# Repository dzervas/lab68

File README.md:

# Dissatisfaction65
<center>
  
</center>
This is the hardware repository for my 65% QMK Bluetooth keyboard with an OLED and encoder.

**I'm working on a new version of this to vastly improve the design and functionality. You can follow the development on [this discord](https://discord.gg/mYy7CFR)**

# Software (QMK)
You can currently find the firmware for this board at [my qmk-firmware fork](https://github.com/Nicell/qmk_firmware/tree/dissatisfaction-65). It requires [this pull-request](https://github.com/qmk/qmk_firmware/pull/7769) before it can be fully upstreamed.

# What you'll need (or at least what I used)
You can get most of these items at different places, but I left the more convenient places here. Often you can get cheaper electronics at LCSC and AliExpress rather than Mouser and Amazon.
 - Adafruit Feather 32u4 Bluefruit LE [BUY](https://www.amazon.com/Adafruit-Feather-32u4-Bluefruit-ADA2829/dp/B01GJR9MNI)
 - 2500mAH battery or equivalent (probably don't go thicker) [BUY](https://www.amazon.com/Adafruit-328-Battery-Lithium-Polymer/dp/B01NAX9XYG)
 - EC12 Encoder Knob [BUY](https://www.amazon.com/Cylewet-Encoder-Digital-Potentiometer-Arduino/dp/B07DM2YMT4)
 - OLED SSD1306 128x32 [BUY](https://www.amazon.com/MakerFocus-Display-SSD1306-3-3V-5V-Arduino/dp/B079BN2J8V)
 - Long headers for the OLED to reach far down [BUY](https://www.mouser.com/ProductDetail/fci-amphenol/68653-105hlf)
 - 1N4148 DO-35 package 67x [BUY](https://www.mouser.com/ProductDetail/on-semiconductor/1n4148tr)
 - 74HC4515 Decoder [BUY](https://www.mouser.com/ProductDetail/nexperia/74hc4515d653)
 - On-Off switch [BUY](https://www.mouser.com/ProductDetail/alps/sddjf1a100)
 - Encoder Knob [BUY](https://www.amazon.com/dp/B07Z1MQ9T7)
 - M3 ([Bolts](https://www.amazon.com/gp/product/B075CFBHWV)) ([Nuts](https://www.amazon.com/gp/product/B01IWUSDYY)) ([Lock Nuts](https://www.amazon.com/gp/product/B07MD7SPBJ)) ([Rubber Feet](https://www.amazon.com/gp/product/B07CNQC695))
 - Plates: one of each of the plates found in the DXF folder. Middle MUST be 1.5mm. I got mine from SendCutSend in brushed stainless steel using the combined plates file. I highly recommend them. Fast, affordable, and good quality.
 - Middle pieces: 7x of the middle piece found in the DXF folder. I used 1/8in thick pieces. 2x between the top and switch plate, and 5x between the bottom and switch plate. The second and third to last from the bottom pieces need cutouts for both the micro USB and the power switch. I got mine from Sculpteo. I would not recommend them. The wait was long, the order was messed up, and the quality was very mediocre. There was an obvious taper on the cuts.
 - MX style switches 67x. PCB or plate mount
 - Keycaps! KLE can be found [here](http://www.keyboard-layout-editor.com/#/gists/c38820c1ede8c90e253ba465600c6e75).

# Things I'd like to change
There were a few things that I'd like to change. I haven't done them yet, but they would enhance the board.
 - Move the encoder switch to the matrix. Currently has its own direct connection.
 - Recreate the switch plate using ai03's plate designer. Currently has huge lines across stabs and the stab holes are really tight.
 - Re-dimension the OLED. It seems to be barely too far down and to the left. I can re-dimension now that I have calipers.
 - Redo the decoder using a 74HC154. No need to use the latched version that's more expensive and slower.
 - Create a little cut in the middle pieces to use as a prop up for the OLED.
 - Create pre-made middle pieces with cutouts for the micro USB port and the on-off switch rather than cutting them manually.

# Random things I encountered
 - Make sure to test your Adafruit board fully before soldering it in. The board I got had a working MCU and Bluetooth module, but they couldn't communicate properly despite continuity between the SPI pins.
 - My plate ended up flexing a bit when connecting the switches. I suspect the PCB was either a bit too small or the plate was a bit too big. I really don't know why this was the case.

# Thanks to
 - QMK team for helping me with getting the firmware working
 - Nick_68 and WoodKeys for each of their iterations on the Bluetooth + decoder design with the Ronin and Meira, which were invaluable for me while I was designing this board.
 - ai03 for the MX KiCad library I have in this project.

OLED 3D Model: https://grabcad.com/library/oled-0-91-128x32-1
Rotary Encoder 3D Model: https://grabcad.com/library/ec11-rotary-encoder-with-switch-1
MX Switches & stabilizers 3D Models: https://github.com/perigoso/keyswitch-kicad-library

# Images

# Fusion 360 Prepare Board Model

1. Export STEP with KicadStepUp (FreeCAD)
2. Import it in an empty document
3. Create a rigid group between all components
4. Align the group to true origin (using 2 faces)

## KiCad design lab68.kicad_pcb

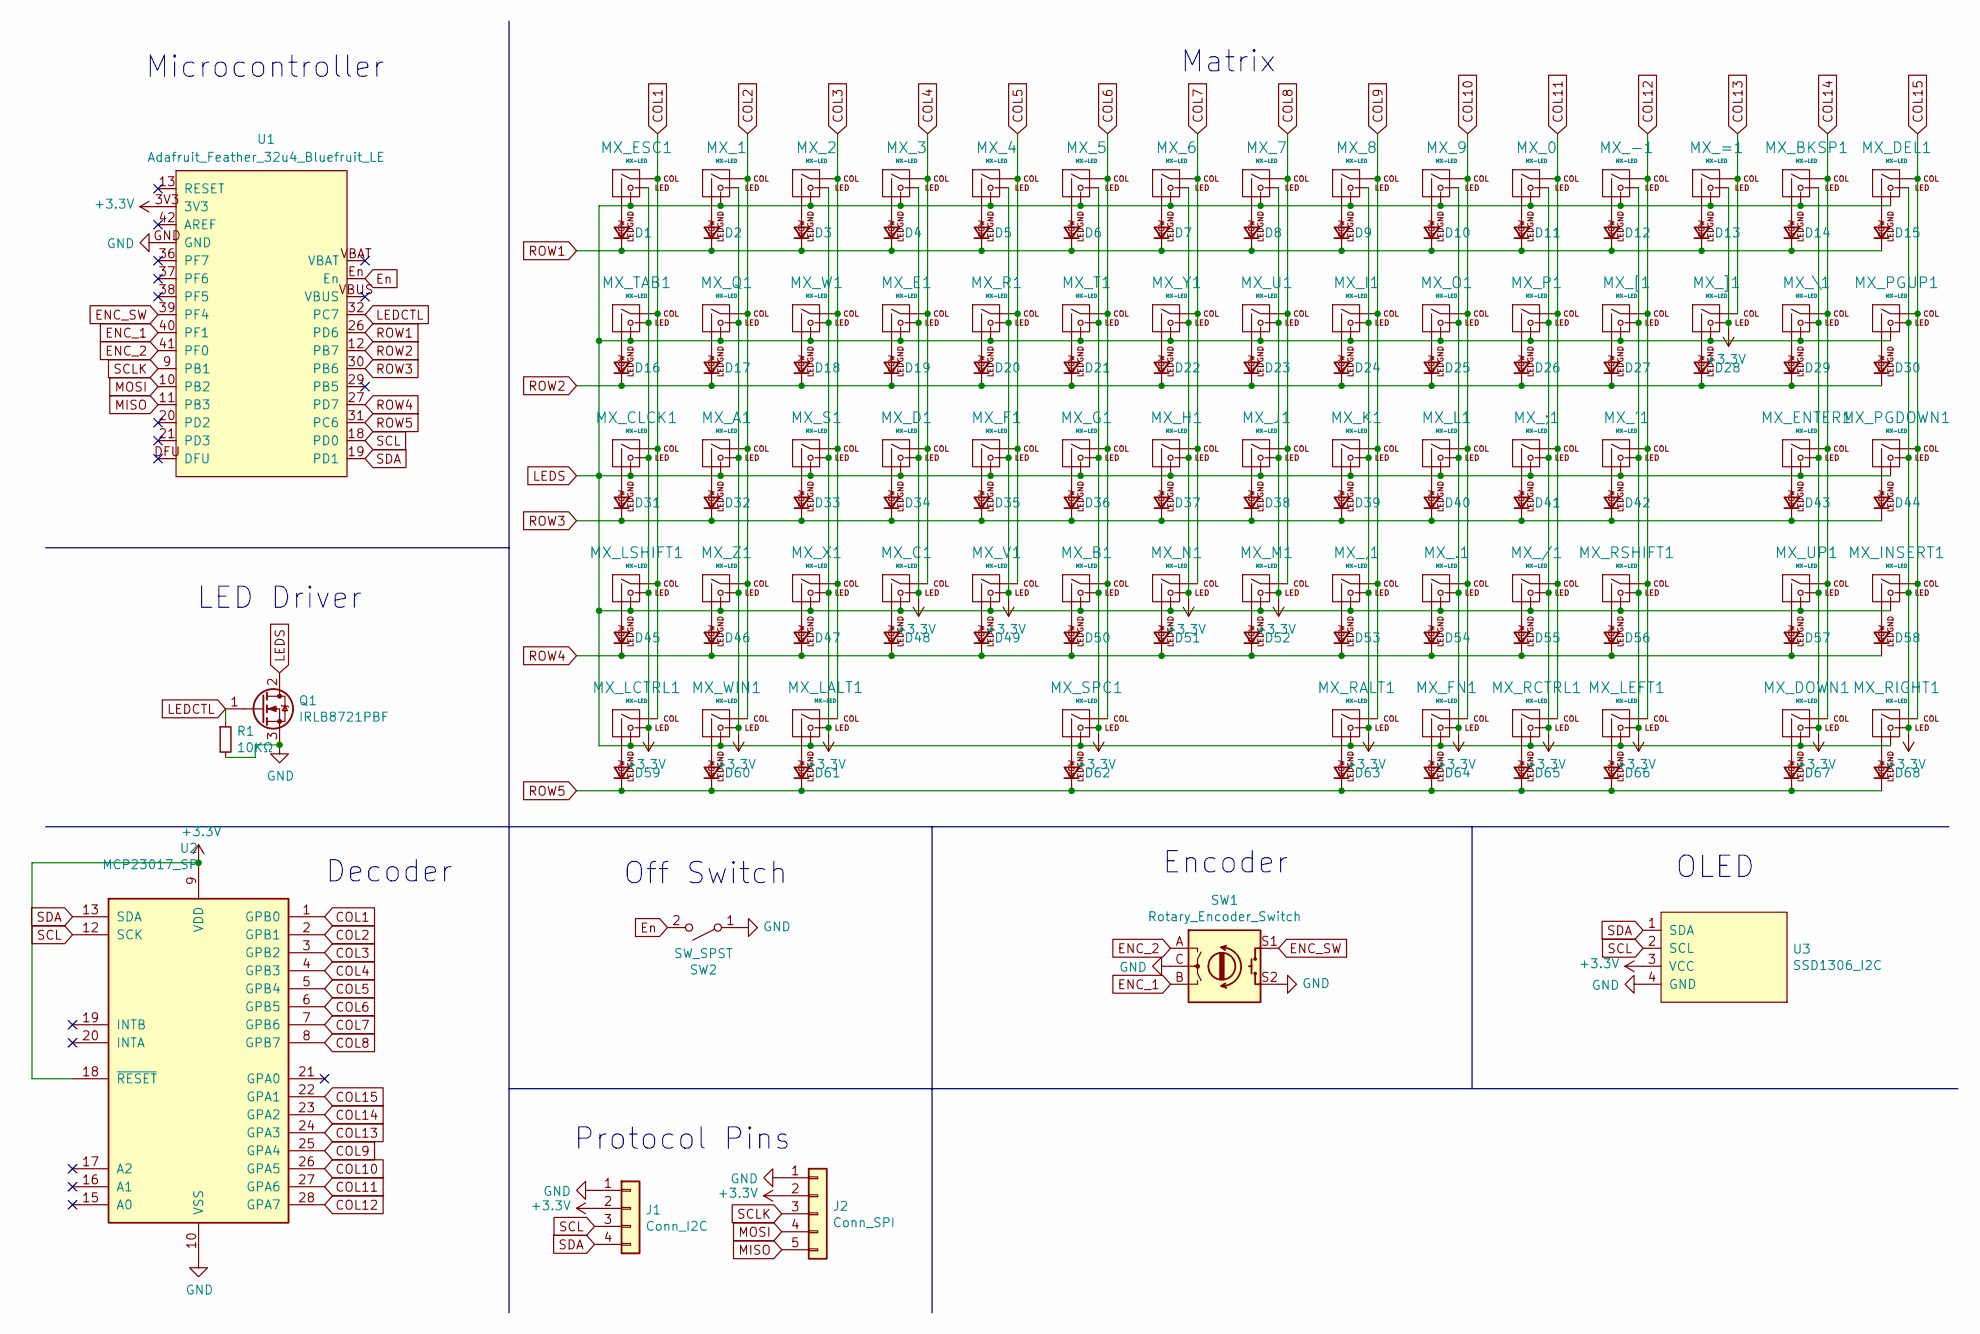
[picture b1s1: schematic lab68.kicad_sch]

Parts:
D1, D2, D3, D4, D5, D6, D7, D8, D9, D10, D11, D12, D13, D14, D15, D16, D17, D18, D19, D20, D21, D22, D23, D24, D25, D26, D27, D28, D29, D30, D31, D32, D33, D34, D35, D36, D37, D38, D39, D40, D41, D42, D43, D44, D45, D46, D47, D48, D49, D50, D51, D52, D53, D54, D55, D56, D57, D58, D59, D60, D61, D62, D63, D64, D65, D66, D67, D68: D_Small; D_DO-35_SOD27_P7.62mm_Horizontal
J1: Conn_I2C; JST_XH_B4B-XH-A_1x04_P2.50mm_Vertical
J2: Conn_SPI; JST_XH_B5B-XH-A_1x05_P2.50mm_Vertical
MX_0, MX_1, MX_2, MX_3, MX_4, MX_5, MX_6, MX_7, MX_8, MX_9, MX_.1: MX-LED; MXOnly-1U
MX_'1: MX-LED; MXOnly-1U
MX_,1: MX-LED; MXOnly-1U
MX_-1: MX-LED; MXOnly-1U
MX_/1: MX-LED; MXOnly-1U
MX_;1: MX-LED; MXOnly-1U
MX_=1: MX-LED; MXOnly-1U
MX_A1: MX-LED; MXOnly-1U
MX_B1: MX-LED; MXOnly-1U
MX_BKSP1: MX-LED; MXOnly-2U
MX_C1: MX-LED; MXOnly-1U
MX_CLCK1: MX-LED; MXOnly-1.75U
MX_D1: MX-LED; MXOnly-1U
MX_DEL1: MX-LED; MXOnly-1U
MX_DOWN1: MX-LED; MXOnly-1U
MX_E1: MX-LED; MXOnly-1U
MX_ENTER1: MX-LED; MXOnly-2.25U
MX_ESC1: MX-LED; MXOnly-1U
MX_F1: MX-LED; MXOnly-1U
MX_FN1: MX-LED; MXOnly-1U
MX_G1: MX-LED; MXOnly-1U
MX_H1: MX-LED; MXOnly-1U
MX_I1: MX-LED; MXOnly-1U
MX_INSERT1: MX-LED; MXOnly-1U
MX_J1: MX-LED; MXOnly-1U
MX_K1: MX-LED; MXOnly-1U
MX_L1: MX-LED; MXOnly-1U
MX_LALT1: MX-LED; MXOnly-1.25U
MX_LCTRL1: MX-LED; MXOnly-1.25U
MX_LEFT1: MX-LED; MXOnly-1U
MX_LSHIFT1: MX-LED; MXOnly-2.25U
MX_M1: MX-LED; MXOnly-1U
MX_N1: MX-LED; MXOnly-1U
MX_O1: MX-LED; MXOnly-1U
MX_P1: MX-LED; MXOnly-1U
MX_PGDOWN1: MX-LED; MXOnly-1U
MX_PGUP1: MX-LED; MXOnly-1U
MX_Q1: MX-LED; MXOnly-1U
MX_R1: MX-LED; MXOnly-1U
MX_RALT1: MX-LED; MXOnly-1U
MX_RCTRL1: MX-LED; MXOnly-1U
MX_RIGHT1: MX-LED; MXOnly-1U
MX_RSHIFT1: MX-LED; MXOnly-1.75U
MX_S1: MX-LED; MXOnly-1U
MX_SPC1: MX-LED; MXOnly-6.25U-ReversedStabilizers
MX_T1: MX-LED; MXOnly-1U
MX_TAB1: MX-LED; MXOnly-1.5U
MX_U1: MX-LED; MXOnly-1U
MX_UP1: MX-LED; MXOnly-1U
MX_V1: MX-LED; MXOnly-1U
MX_W1: MX-LED; MXOnly-1U
MX_WIN1: MX-LED; MXOnly-1.25U
MX_X1: MX-LED; MXOnly-1U
MX_Y1: MX-LED; MXOnly-1U
MX_Z1: MX-LED; MXOnly-1U
MX_[1: MX-LED; MXOnly-1U
MX_\1: MX-LED; MXOnly-1.5U
MX_]1: MX-LED; MXOnly-1U
Q1: IRLB8721PBF; TO-220-3_Horizontal_TabDown
R1: 10KΩ; R_Axial_DIN0207_L6.3mm_D2.5mm_P7.62mm_Horizontal
SW1: Rotary_Encoder_Switch; RotaryEncoder_Alps_EC11E-Switch_Vertical_H20mm
SW2: SW_SPST; SW_CuK_JS202011AQN_DPDT_Angled
U1: Adafruit_Feather_32u4_Bluefruit_LE
U2: MCP23017_SP; DIP-28_W7.62mm_Socket_LongPads
U3: SSD1306_I2C; OLED

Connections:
+3V3: J1.2, J2.2, MX_0.3 (LED), MX_1.3 (LED), MX_2.3 (LED), MX_3.3 (LED), MX_4.3 (LED), MX_5.3 (LED), MX_6.3 (LED), MX_7.3 (LED), MX_8.3 (LED), MX_9.3 (LED), MX_'1.3 (LED), MX_,1.3 (LED), MX_-1.3 (LED), MX_.1.3 (LED), MX_/1.3 (LED), MX_;1.3 (LED), MX_=1.3 (LED), MX_A1.3 (LED), MX_B1.3 (LED), MX_BKSP1.3 (LED), MX_C1.3 (LED), MX_CLCK1.3 (LED), MX_D1.3 (LED), MX_DEL1.3 (LED), MX_DOWN1.3 (LED), MX_E1.3 (LED), MX_ENTER1.3 (LED), MX_ESC1.3 (LED), MX_F1.3 (LED), MX_FN1.3 (LED), MX_G1.3 (LED), MX_H1.3 (LED), MX_I1.3 (LED), MX_INSERT1.3 (LED), MX_J1.3 (LED), MX_K1.3 (LED), MX_L1.3 (LED), MX_LALT1.3 (LED), MX_LCTRL1.3 (LED), MX_LEFT1.3 (LED), MX_LSHIFT1.3 (LED), MX_M1.3 (LED), MX_N1.3 (LED), MX_O1.3 (LED), MX_P1.3 (LED), MX_PGDOWN1.3 (LED), MX_PGUP1.3 (LED), MX_Q1.3 (LED), MX_R1.3 (LED), MX_RALT1.3 (LED), MX_RCTRL1.3 (LED), MX_RIGHT1.3 (LED), MX_RSHIFT1.3 (LED), MX_S1.3 (LED), MX_SPC1.3 (LED), MX_T1.3 (LED), MX_TAB1.3 (LED), MX_U1.3 (LED), MX_UP1.3 (LED), MX_V1.3 (LED), MX_W1.3 (LED), MX_WIN1.3 (LED), MX_X1.3 (LED), MX_Y1.3 (LED), MX_Z1.3 (LED), MX_[1.3 (LED), MX_\1.3 (LED), MX_]1.3 (LED), U1.3V3, U2.9 (VDD), U2.18 (~RESET), U3.3 (VCC)
COL1: MX_CLCK1.1 (COL), MX_ESC1.1 (COL), MX_LCTRL1.1 (COL), MX_LSHIFT1.1 (COL), MX_TAB1.1 (COL), U2.1 (GPB0)
COL2: MX_1.1 (COL), MX_A1.1 (COL), MX_Q1.1 (COL), MX_WIN1.1 (COL), MX_Z1.1 (COL), U2.2 (GPB1)
COL3: MX_2.1 (COL), MX_LALT1.1 (COL), MX_S1.1 (COL), MX_W1.1 (COL), MX_X1.1 (COL), U2.3 (GPB2)
COL4: MX_3.1 (COL), MX_C1.1 (COL), MX_D1.1 (COL), MX_E1.1 (COL), U2.4 (GPB3)
COL5: MX_4.1 (COL), MX_F1.1 (COL), MX_R1.1 (COL), MX_V1.1 (COL), U2.5 (GPB4)
COL6: MX_5.1 (COL), MX_B1.1 (COL), MX_G1.1 (COL), MX_SPC1.1 (COL), MX_T1.1 (COL), U2.6 (GPB5)
COL7: MX_6.1 (COL), MX_H1.1 (COL), MX_N1.1 (COL), MX_Y1.1 (COL), U2.7 (GPB6)
COL8: MX_7.1 (COL), MX_J1.1 (COL), MX_M1.1 (COL), MX_U1.1 (COL), U2.8 (GPB7)
COL9: MX_8.1 (COL), MX_,1.1 (COL), MX_I1.1 (COL), MX_K1.1 (COL), MX_RALT1.1 (COL), U2.25 (GPA4)
COL10: MX_9.1 (COL), MX_.1.1 (COL), MX_FN1.1 (COL), MX_L1.1 (COL), MX_O1.1 (COL), U2.26 (GPA5)
COL11: MX_0.1 (COL), MX_/1.1 (COL), MX_;1.1 (COL), MX_P1.1 (COL), MX_RCTRL1.1 (COL), U2.27 (GPA6)
COL12: MX_'1.1 (COL), MX_-1.1 (COL), MX_LEFT1.1 (COL), MX_RSHIFT1.1 (COL), MX_[1.1 (COL), U2.28 (GPA7)
COL13: MX_=1.1 (COL), MX_]1.1 (COL), U2.24 (GPA3)
COL14: MX_BKSP1.1 (COL), MX_DOWN1.1 (COL), MX_ENTER1.1 (COL), MX_UP1.1 (COL), MX_\1.1 (COL), U2.23 (GPA2)
COL15: MX_DEL1.1 (COL), MX_INSERT1.1 (COL), MX_PGDOWN1.1 (COL), MX_PGUP1.1 (COL), MX_RIGHT1.1 (COL), U2.22 (GPA1)
ENC_1: SW1.B, U1.40 (PF1)
ENC_2: SW1.A, U1.41 (PF0)
ENC_SW: SW1.S1, U1.39 (PF4)
En: SW2.2 (B), U1.En
GND: J1.1, J2.1, Q1.3 (S), R1.2, SW1.C, SW1.S2, SW2.1 (A), U1.GND, U2.10 (VSS), U3.4 (GND)
LEDCTL: Q1.1 (G), R1.1, U1.32 (PC7)
LEDS: MX_0.4 (LEDGND), MX_1.4 (LEDGND), MX_2.4 (LEDGND), MX_3.4 (LEDGND), MX_4.4 (LEDGND), MX_5.4 (LEDGND), MX_6.4 (LEDGND), MX_7.4 (LEDGND), MX_8.4 (LEDGND), MX_9.4 (LEDGND), MX_'1.4 (LEDGND), MX_,1.4 (LEDGND), MX_-1.4 (LEDGND), MX_.1.4 (LEDGND), MX_/1.4 (LEDGND), MX_;1.4 (LEDGND), MX_=1.4 (LEDGND), MX_A1.4 (LEDGND), MX_B1.4 (LEDGND), MX_BKSP1.4 (LEDGND), MX_C1.4 (LEDGND), MX_CLCK1.4 (LEDGND), MX_D1.4 (LEDGND), MX_DEL1.4 (LEDGND), MX_DOWN1.4 (LEDGND), MX_E1.4 (LEDGND), MX_ENTER1.4 (LEDGND), MX_ESC1.4 (LEDGND), MX_F1.4 (LEDGND), MX_FN1.4 (LEDGND), MX_G1.4 (LEDGND), MX_H1.4 (LEDGND), MX_I1.4 (LEDGND), MX_INSERT1.4 (LEDGND), MX_J1.4 (LEDGND), MX_K1.4 (LEDGND), MX_L1.4 (LEDGND), MX_LALT1.4 (LEDGND), MX_LCTRL1.4 (LEDGND), MX_LEFT1.4 (LEDGND), MX_LSHIFT1.4 (LEDGND), MX_M1.4 (LEDGND), MX_N1.4 (LEDGND), MX_O1.4 (LEDGND), MX_P1.4 (LEDGND), MX_PGDOWN1.4 (LEDGND), MX_PGUP1.4 (LEDGND), MX_Q1.4 (LEDGND), MX_R1.4 (LEDGND), MX_RALT1.4 (LEDGND), MX_RCTRL1.4 (LEDGND), MX_RIGHT1.4 (LEDGND), MX_RSHIFT1.4 (LEDGND), MX_S1.4 (LEDGND), MX_SPC1.4 (LEDGND), MX_T1.4 (LEDGND), MX_TAB1.4 (LEDGND), MX_U1.4 (LEDGND), MX_UP1.4 (LEDGND), MX_V1.4 (LEDGND), MX_W1.4 (LEDGND), MX_WIN1.4 (LEDGND), MX_X1.4 (LEDGND), MX_Y1.4 (LEDGND), MX_Z1.4 (LEDGND), MX_[1.4 (LEDGND), MX_\1.4 (LEDGND), MX_]1.4 (LEDGND), Q1.2 (D)
MISO: J2.5, U1.11 (PB3)
MOSI: J2.4, U1.10 (PB2)
unnamed: D1.2 (A), MX_ESC1.2 (ROW)
unnamed: D2.2 (A), MX_1.2 (ROW)
unnamed: D3.2 (A), MX_2.2 (ROW)
unnamed: D4.2 (A), MX_3.2 (ROW)
unnamed: D5.2 (A), MX_4.2 (ROW)
unnamed: D6.2 (A), MX_5.2 (ROW)
unnamed: D7.2 (A), MX_6.2 (ROW)
unnamed: D8.2 (A), MX_7.2 (ROW)
unnamed: D9.2 (A), MX_8.2 (ROW)
unnamed: D10.2 (A), MX_9.2 (ROW)
unnamed: D11.2 (A), MX_0.2 (ROW)
unnamed: D12.2 (A), MX_-1.2 (ROW)
unnamed: D13.2 (A), MX_=1.2 (ROW)
unnamed: D14.2 (A), MX_BKSP1.2 (ROW)
unnamed: D15.2 (A), MX_DEL1.2 (ROW)
unnamed: D16.2 (A), MX_TAB1.2 (ROW)
unnamed: D17.2 (A), MX_Q1.2 (ROW)
unnamed: D18.2 (A), MX_W1.2 (ROW)
unnamed: D19.2 (A), MX_E1.2 (ROW)
unnamed: D20.2 (A), MX_R1.2 (ROW)
unnamed: D21.2 (A), MX_T1.2 (ROW)
unnamed: D22.2 (A), MX_Y1.2 (ROW)
unnamed: D23.2 (A), MX_U1.2 (ROW)
unnamed: D24.2 (A), MX_I1.2 (ROW)
unnamed: D25.2 (A), MX_O1.2 (ROW)
unnamed: D26.2 (A), MX_P1.2 (ROW)
unnamed: D27.2 (A), MX_[1.2 (ROW)
unnamed: D28.2 (A), MX_]1.2 (ROW)
unnamed: D29.2 (A), MX_\1.2 (ROW)
unnamed: D30.2 (A), MX_PGUP1.2 (ROW)
unnamed: D31.2 (A), MX_CLCK1.2 (ROW)
unnamed: D32.2 (A), MX_A1.2 (ROW)
unnamed: D33.2 (A), MX_S1.2 (ROW)
unnamed: D34.2 (A), MX_D1.2 (ROW)
unnamed: D35.2 (A), MX_F1.2 (ROW)
unnamed: D36.2 (A), MX_G1.2 (ROW)
unnamed: D37.2 (A), MX_H1.2 (ROW)
unnamed: D38.2 (A), MX_J1.2 (ROW)
unnamed: D39.2 (A), MX_K1.2 (ROW)
unnamed: D40.2 (A), MX_L1.2 (ROW)
unnamed: D41.2 (A), MX_;1.2 (ROW)
unnamed: D42.2 (A), MX_'1.2 (ROW)
unnamed: D43.2 (A), MX_ENTER1.2 (ROW)
unnamed: D44.2 (A), MX_PGDOWN1.2 (ROW)
unnamed: D45.2 (A), MX_LSHIFT1.2 (ROW)
unnamed: D46.2 (A), MX_Z1.2 (ROW)
unnamed: D47.2 (A), MX_X1.2 (ROW)
unnamed: D48.2 (A), MX_C1.2 (ROW)
unnamed: D49.2 (A), MX_V1.2 (ROW)
unnamed: D50.2 (A), MX_B1.2 (ROW)
unnamed: D51.2 (A), MX_N1.2 (ROW)
unnamed: D52.2 (A), MX_M1.2 (ROW)
unnamed: D53.2 (A), MX_,1.2 (ROW)
unnamed: D54.2 (A), MX_.1.2 (ROW)
unnamed: D55.2 (A), MX_/1.2 (ROW)
unnamed: D56.2 (A), MX_RSHIFT1.2 (ROW)
unnamed: D57.2 (A), MX_UP1.2 (ROW)
unnamed: D58.2 (A), MX_INSERT1.2 (ROW)
unnamed: D59.2 (A), MX_LCTRL1.2 (ROW)
unnamed: D60.2 (A), MX_WIN1.2 (ROW)
unnamed: D61.2 (A), MX_LALT1.2 (ROW)
unnamed: D62.2 (A), MX_SPC1.2 (ROW)
unnamed: D63.2 (A), MX_RALT1.2 (ROW)
unnamed: D64.2 (A), MX_FN1.2 (ROW)
unnamed: D65.2 (A), MX_RCTRL1.2 (ROW)
unnamed: D66.2 (A), MX_LEFT1.2 (ROW)
unnamed: D67.2 (A), MX_DOWN1.2 (ROW)
unnamed: D68.2 (A), MX_RIGHT1.2 (ROW)
ROW1: D1.1 (K), D2.1 (K), D3.1 (K), D4.1 (K), D5.1 (K), D6.1 (K), D7.1 (K), D8.1 (K), D9.1 (K), D10.1 (K), D11.1 (K), D12.1 (K), D13.1 (K), D14.1 (K), D15.1 (K), U1.26 (PD6)
ROW2: D16.1 (K), D17.1 (K), D18.1 (K), D19.1 (K), D20.1 (K), D21.1 (K), D22.1 (K), D23.1 (K), D24.1 (K), D25.1 (K), D26.1 (K), D27.1 (K), D28.1 (K), D29.1 (K), D30.1 (K), U1.12 (PB7)
ROW3: D31.1 (K), D32.1 (K), D33.1 (K), D34.1 (K), D35.1 (K), D36.1 (K), D37.1 (K), D38.1 (K), D39.1 (K), D40.1 (K), D41.1 (K), D42.1 (K), D43.1 (K), D44.1 (K), U1.30 (PB6)
ROW4: D45.1 (K), D46.1 (K), D47.1 (K), D48.1 (K), D49.1 (K), D50.1 (K), D51.1 (K), D52.1 (K), D53.1 (K), D54.1 (K), D55.1 (K), D56.1 (K), D57.1 (K), D58.1 (K), U1.27 (PD7)
ROW5: D59.1 (K), D60.1 (K), D61.1 (K), D62.1 (K), D63.1 (K), D64.1 (K), D65.1 (K), D66.1 (K), D67.1 (K), D68.1 (K), U1.31 (PC6)
SCL: J1.3, U1.18 (PD0), U2.12 (SCK), U3.2 (SCL)
SCLK: J2.3, U1.9 (PB1)
SDA: J1.4, U1.19 (PD1), U2.13 (SDA), U3.1 (SDA)

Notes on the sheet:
Decoder
Encoder
Matrix
LED Driver
Microcontroller
Protocol Pins
OLED
Off Switch

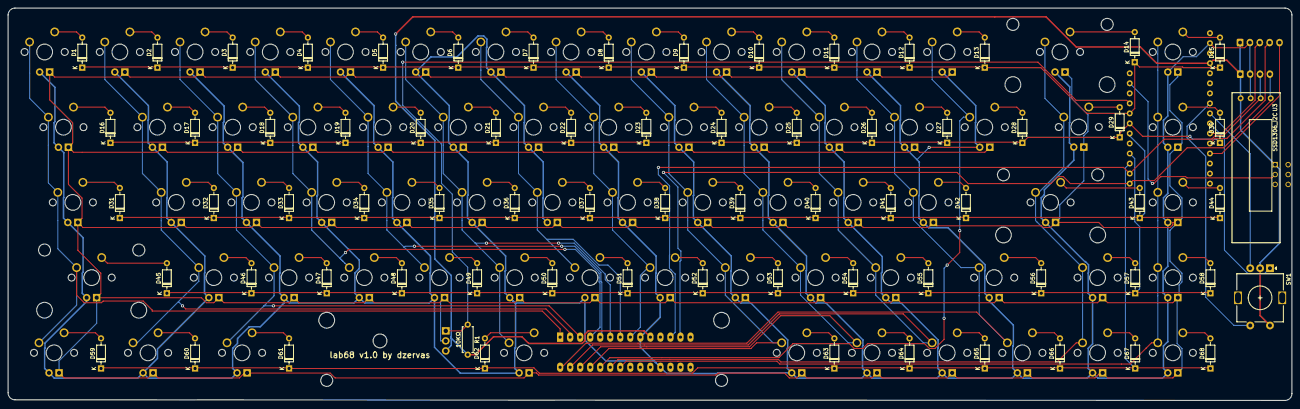
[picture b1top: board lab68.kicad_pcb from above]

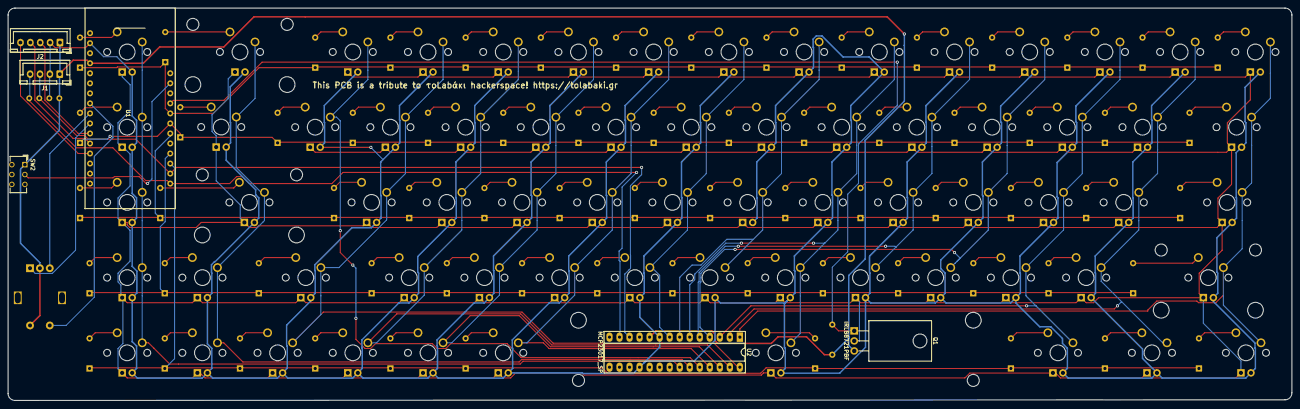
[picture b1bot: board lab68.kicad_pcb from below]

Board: 2 copper layers, 325.2 x 99.4 mm, 145 parts (6 on the bottom side), 101 nets.

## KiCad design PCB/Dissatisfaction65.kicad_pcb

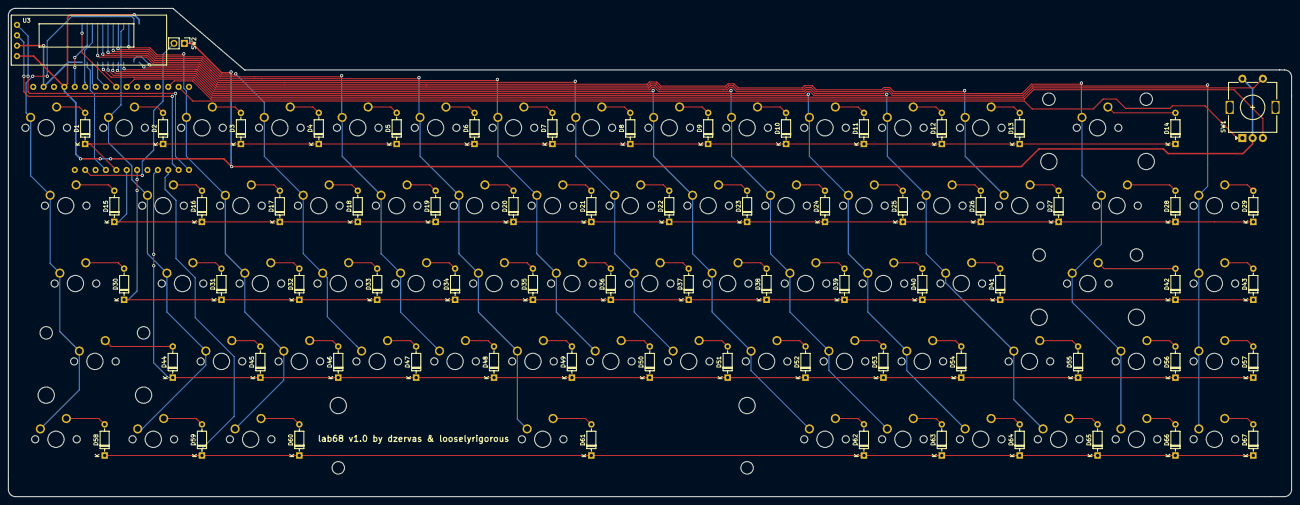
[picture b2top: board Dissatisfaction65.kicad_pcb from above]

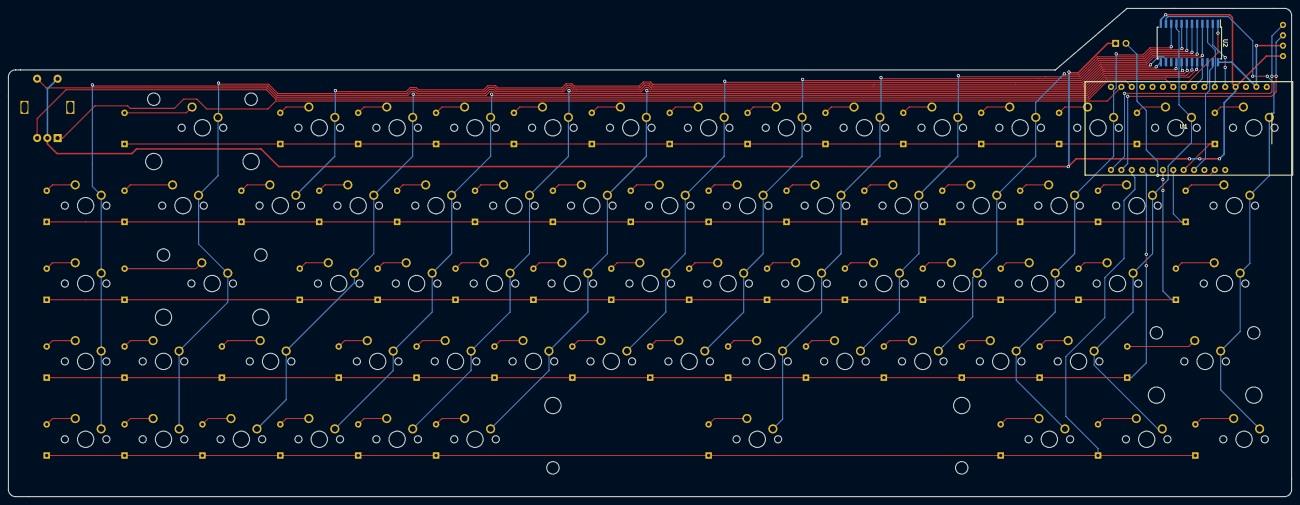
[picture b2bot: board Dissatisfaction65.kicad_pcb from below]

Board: 2 copper layers, 313.9 x 119.4 mm, 139 parts (2 on the bottom side), 101 nets.

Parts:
D1, D2, D3, D4, D5, D6, D7, D8, D9, D10, D11, D12, D13, D14, D15, D16, D17, D18, D19, D20, D21, D22, D23, D24, D25, D26, D27, D28, D29, D30, D31, D32, D33, D34, D35, D36, D37, D38, D39, D40, D41, D42, D43, D44, D45, D46, D47, D48, D49, D50, D51, D52, D53, D54, D55, D56, D57, D58, D59, D60, D61, D62, D63, D64, D65, D66, D67: D_Small; D_DO-35_SOD27_P7.62mm_Horizontal
MX_0, MX_1, MX_2, MX_3, MX_4, MX_5, MX_6, MX_7, MX_8, MX_9, MX_.1: MX-NoLED; MXOnly-1U-NoLED
MX_'1: MX-NoLED; MXOnly-1U-NoLED
MX_,1: MX-NoLED; MXOnly-1U-NoLED
MX_-1: MX-NoLED; MXOnly-1U-NoLED
MX_/1: MX-NoLED; MXOnly-1U-NoLED
MX_;1: MX-NoLED; MXOnly-1U-NoLED
MX_=1: MX-NoLED; MXOnly-1U-NoLED
MX_A1: MX-NoLED; MXOnly-1U-NoLED
MX_B1: MX-NoLED; MXOnly-1U-NoLED
MX_BKSP1: MX-NoLED; MXOnly-2U-NoLED
MX_C1: MX-NoLED; MXOnly-1U-NoLED
MX_CLCK1: MX-NoLED; MXOnly-1.75U-NoLED
MX_D1: MX-NoLED; MXOnly-1U-NoLED
MX_DEL1: MX-NoLED; MXOnly-1U-NoLED
MX_DOWN1: MX-NoLED; MXOnly-1U-NoLED
MX_E1: MX-NoLED; MXOnly-1U-NoLED
MX_END1: MX-NoLED; MXOnly-1U-NoLED
MX_ENTER1: MX-NoLED; MXOnly-2.25U-NoLED
MX_ESC1: MX-NoLED; MXOnly-1U-NoLED
MX_F1: MX-NoLED; MXOnly-1U-NoLED
MX_FN1: MX-NoLED; MXOnly-1U-NoLED
MX_G1: MX-NoLED; MXOnly-1U-NoLED
MX_H1: MX-NoLED; MXOnly-1U-NoLED
MX_HOME1: MX-NoLED; MXOnly-1U-NoLED
MX_I1: MX-NoLED; MXOnly-1U-NoLED
MX_J1: MX-NoLED; MXOnly-1U-NoLED
MX_K1: MX-NoLED; MXOnly-1U-NoLED
MX_L1: MX-NoLED; MXOnly-1U-NoLED
MX_LALT1: MX-NoLED; MXOnly-1.25U-NoLED
MX_LCTRL1: MX-NoLED; MXOnly-1.25U-NoLED
MX_LEFT1: MX-NoLED; MXOnly-1U-NoLED
MX_LSHIFT1: MX-NoLED; MXOnly-2.25U-NoLED
MX_M1: MX-NoLED; MXOnly-1U-NoLED
MX_N1: MX-NoLED; MXOnly-1U-NoLED
MX_O1: MX-NoLED; MXOnly-1U-NoLED
MX_P1: MX-NoLED; MXOnly-1U-NoLED
MX_Q1: MX-NoLED; MXOnly-1U-NoLED
MX_R1: MX-NoLED; MXOnly-1U-NoLED
MX_RALT1: MX-NoLED; MXOnly-1U-NoLED
MX_RCTRL1: MX-NoLED; MXOnly-1U-NoLED
MX_RIGHT1: MX-NoLED; MXOnly-1U-NoLED
MX_RSHIFT1: MX-NoLED; MXOnly-1.75U-NoLED
MX_S1: MX-NoLED; MXOnly-1U-NoLED
MX_SPC1: MX-NoLED; MXOnly-6.25U-ReversedStabilizers-NoLED
MX_T1: MX-NoLED; MXOnly-1U-NoLED
MX_TAB1: MX-NoLED; MXOnly-1.5U-NoLED
MX_U1: MX-NoLED; MXOnly-1U-NoLED
MX_UP1: MX-NoLED; MXOnly-1U-NoLED
MX_V1: MX-NoLED; MXOnly-1U-NoLED
MX_W1: MX-NoLED; MXOnly-1U-NoLED
MX_WIN1: MX-NoLED; MXOnly-1.25U-NoLED
MX_X1: MX-NoLED; MXOnly-1U-NoLED
MX_Y1: MX-NoLED; MXOnly-1U-NoLED
MX_Z1: MX-NoLED; MXOnly-1U-NoLED
MX_[1: MX-NoLED; MXOnly-1U-NoLED
MX_\1: MX-NoLED; MXOnly-1.5U-NoLED
MX_]1: MX-NoLED; MXOnly-1U-NoLED
SW1: Rotary_Encoder_Switch; RotaryEncoder_Alps_EC11E-Switch_Vertical_H20mm
SW2: SW_SPST; PinHeader_1x02_P2.54mm_Vertical
U1: Adafruit_Feather_32u4_Bluefruit_LE
U2: 74HC4514; SOIC-24W_7.5x15.4mm_P1.27mm
U3: SSD1306_I2C; OLED

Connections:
3v3: U1.3V3, U2.24, U3.3
CLD1: U1.36, U2.2
CLD2: U1.37, U2.3
CLD3: U1.39, U2.21
CLD4: U1.38, U2.22
COL1: MX_CLCK1.1, MX_ESC1.1, MX_LCTRL1.1, MX_LSHIFT1.1, MX_TAB1.1, U2.11
COL2: MX_1.1, MX_A1.1, MX_Q1.1, MX_WIN1.1, MX_Z1.1, U2.9
COL3: MX_2.1, MX_LALT1.1, MX_S1.1, MX_W1.1, MX_X1.1, U2.10
COL4: MX_3.1, MX_C1.1, MX_D1.1, MX_E1.1, U2.8
COL5: MX_4.1, MX_F1.1, MX_R1.1, MX_V1.1, U2.7
COL6: MX_5.1, MX_B1.1, MX_G1.1, MX_SPC1.1, MX_T1.1, U2.6
COL7: MX_6.1, MX_H1.1, MX_N1.1, MX_Y1.1, U2.5
COL8: MX_7.1, MX_J1.1, MX_M1.1, MX_U1.1, U2.4
COL9: MX_8.1, MX_,1.1, MX_I1.1, MX_K1.1, MX_RALT1.1, U2.18
COL10: MX_9.1, MX_.1.1, MX_FN1.1, MX_L1.1, MX_O1.1, U2.17
COL11: MX_0.1, MX_/1.1, MX_;1.1, MX_P1.1, MX_RCTRL1.1, U2.20
COL12: MX_'1.1, MX_-1.1, MX_LEFT1.1, MX_RSHIFT1.1, MX_[1.1, U2.19
COL13: MX_=1.1, MX_]1.1, U2.14
COL14: MX_BKSP1.1, MX_DOWN1.1, MX_ENTER1.1, MX_UP1.1, MX_\1.1, U2.13
COL15: MX_DEL1.1, MX_END1.1, MX_HOME1.1, MX_RIGHT1.1, U2.16
E: U1.32, U2.23
ENC_1: SW1.B, U1.20
ENC_2: SW1.A, U1.21
ENC_SW: SW1.S1, U1.41
En: SW2.2, U1.En
GND: SW1.C, SW1.S2, SW2.1, U1.GND, U2.12, U3.4
LE: U1.40, U2.1
unnamed: D1.2, MX_ESC1.2
unnamed: D2.2, MX_1.2
unnamed: D3.2, MX_2.2
unnamed: D4.2, MX_3.2
unnamed: D5.2, MX_4.2
unnamed: D6.2, MX_5.2
unnamed: D7.2, MX_6.2
unnamed: D8.2, MX_7.2
unnamed: D9.2, MX_8.2
unnamed: D10.2, MX_9.2
unnamed: D11.2, MX_0.2
unnamed: D12.2, MX_-1.2
unnamed: D13.2, MX_=1.2
unnamed: D14.2, MX_BKSP1.2
unnamed: D15.2, MX_TAB1.2
unnamed: D16.2, MX_Q1.2
unnamed: D17.2, MX_W1.2
unnamed: D18.2, MX_E1.2
unnamed: D19.2, MX_R1.2
unnamed: D20.2, MX_T1.2
unnamed: D21.2, MX_Y1.2
unnamed: D22.2, MX_U1.2
unnamed: D23.2, MX_I1.2
unnamed: D24.2, MX_O1.2
unnamed: D25.2, MX_P1.2
unnamed: D26.2, MX_[1.2
unnamed: D27.2, MX_]1.2
unnamed: D28.2, MX_\1.2
unnamed: D29.2, MX_DEL1.2
unnamed: D30.2, MX_CLCK1.2
unnamed: D31.2, MX_A1.2
unnamed: D32.2, MX_S1.2
unnamed: D33.2, MX_D1.2
unnamed: D34.2, MX_F1.2
unnamed: D35.2, MX_G1.2
unnamed: D36.2, MX_H1.2
unnamed: D37.2, MX_J1.2
unnamed: D38.2, MX_K1.2
unnamed: D39.2, MX_L1.2
unnamed: D40.2, MX_;1.2
unnamed: D41.2, MX_'1.2
unnamed: D42.2, MX_ENTER1.2
unnamed: D43.2, MX_HOME1.2
unnamed: D44.2, MX_LSHIFT1.2
unnamed: D45.2, MX_Z1.2
unnamed: D46.2, MX_X1.2
unnamed: D47.2, MX_C1.2
unnamed: D48.2, MX_V1.2
unnamed: D49.2, MX_B1.2
unnamed: D50.2, MX_N1.2
unnamed: D51.2, MX_M1.2
unnamed: D52.2, MX_,1.2
unnamed: D53.2, MX_.1.2
unnamed: D54.2, MX_/1.2
unnamed: D55.2, MX_RSHIFT1.2
unnamed: D56.2, MX_UP1.2
unnamed: D57.2, MX_END1.2
unnamed: D58.2, MX_LCTRL1.2
unnamed: D59.2, MX_WIN1.2
unnamed: D60.2, MX_LALT1.2
unnamed: D61.2, MX_SPC1.2
unnamed: D62.2, MX_RALT1.2
unnamed: D63.2, MX_FN1.2
unnamed: D64.2, MX_RCTRL1.2
unnamed: D65.2, MX_LEFT1.2
unnamed: D66.2, MX_DOWN1.2
unnamed: D67.2, MX_RIGHT1.2
ROW1: D1.1, D2.1, D3.1, D4.1, D5.1, D6.1, D7.1, D8.1, D9.1, D10.1, D11.1, D12.1, D13.1, D14.1, U1.26
ROW2: D15.1, D16.1, D17.1, D18.1, D19.1, D20.1, D21.1, D22.1, D23.1, D24.1, D25.1, D26.1, D27.1, D28.1, D29.1, U1.12
ROW3: D30.1, D31.1, D32.1, D33.1, D34.1, D35.1, D36.1, D37.1, D38.1, D39.1, D40.1, D41.1, D42.1, D43.1, U1.30
ROW4: D44.1, D45.1, D46.1, D47.1, D48.1, D49.1, D50.1, D51.1, D52.1, D53.1, D54.1, D55.1, D56.1, D57.1, U1.27
ROW5: D58.1, D59.1, D60.1, D61.1, D62.1, D63.1, D64.1, D65.1, D66.1, D67.1, U1.31
SCL: U1.18, U3.2
SDA: U1.19, U3.1

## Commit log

2020-07-22 Partially move to TADA68 layout - still figuring out what to do with the encoder and the screen
2020-07-25 Rename the KiCad project
2020-07-26 Route the LED matrix, change to MCP23017 and add I2C & SPI connectors
2020-07-27 New schematic with global LED illumination - PCB not done yet
2020-07-27 PCB routed! YEY! Now someone has to proof check it
2020-07-27 Tiny fixes - mainly power symbols
2020-07-28 Squashed commit that rearages all the project
    Slight cleanup of the traces on the screen
    Moved feather 1 key right to avoid switch colliding with the feather
    pins on the front side
    Move SPI & I2C connectors to the back
    Updated the switche's footprint and placed it on the right side
    Chage the folder structure
2020-07-29 Move the MCP a bit to the left to avoid collision with stabilizers
2020-07-29 Remove single pad nets
2020-07-29 Initial github action for new board version
2020-07-29 Fix a DRC error
2020-07-29 Do not generate BOM on new release
2020-07-29 Combine ERC & DRC steps and combine the layers of the board on PDF
2020-07-29 Bump version during release
2020-07-30 Add github action config
2020-07-30 Bump board version to 1.1
2020-07-30 Fix board cuts to be closed loop and not angled
2020-08-14 Fix MCP connection bug - only schematic
2020-09-01 Connect the MCP23017 address pins to ground
2020-09-02 Move OLED a bit higher
2020-09-09 Changes?
2020-09-11 Ignore HTML BOM files
2020-09-22 Move the rotary encoder to the right a bit
2020-12-08 Fix the outline
2020-12-08 Make OLED pads bigger, connect MCP interrupts
2020-12-08 Use kikit for CI
2020-12-09 Create a zip of the gerbers
2020-12-09 Bump board version to
2021-10-11 Change switch library and fix 3D models
2021-10-11 Fix OLED & feather 3d models
2021-10-11 Fix outline
2021-10-25 Add case files
2023-11-28 No idea
